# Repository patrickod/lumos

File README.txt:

A simple LED backlight for my monitor

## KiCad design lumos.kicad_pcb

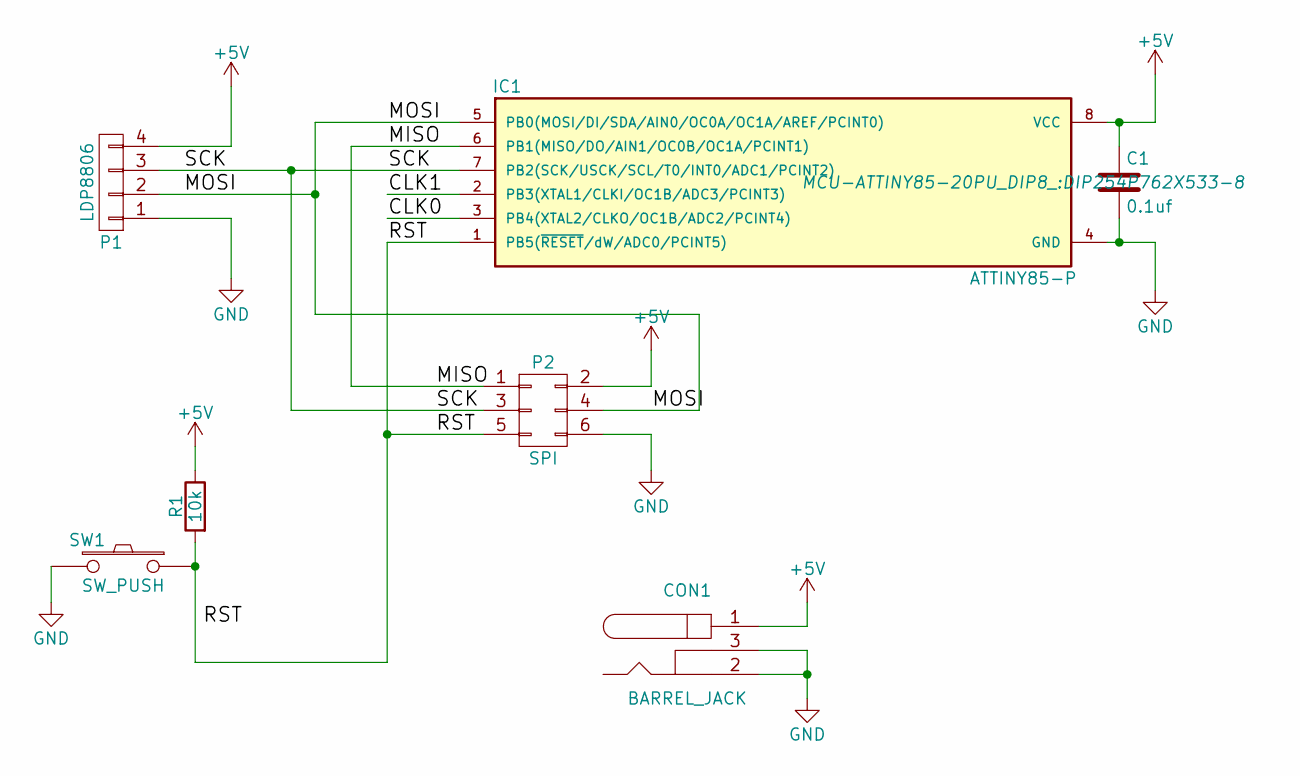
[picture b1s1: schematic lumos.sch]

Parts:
C1: 0.1uf; C_Disc_D7.5_P5
CON1: BARREL_JACK
IC1: ATTINY85-P; DIP254P762X533-8
P1: LDP8806; Pin_Header_Straight_1x04
P2: SPI; Pin_Header_Straight_2x03
R1: 10k; Resistor_Vertical_RM5mm
SW1: SW_PUSH; SW_PUSH_SMALL

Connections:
+5V: C1.1, CON1.1, IC1.8 (VCC), P1.4, P2.2, R1.1
/CLK0: IC1.3 (PB4(XTAL2/CLKO/OC1B/ADC2/PCINT4))
/CLK1: IC1.2 (PB3(XTAL1/CLKI/OC1B/ADC3/PCINT3))
/MISO: IC1.6 (PB1(MISO/DO/AIN1/OC0B/OC1A/PCINT1)), P2.1
/MOSI: IC1.5 (PB0(MOSI/DI/SDA/AIN0/OC0A/OC1A/AREF/PCI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), P1.2, P2.4
/RST: IC1.1 (PB5(~RESET~/dW/ADC0/PCINT5)), P2.5, R1.2, SW1.1
/SCK: IC1.7 (PB2(SCK/USCK/SCL/T0/INT0/ADC1/PCINT2)), P1.3, P2.3
GND: C1.2, CON1.2, CON1.3, IC1.4 (GND), P1.1, P2.6, SW1.2

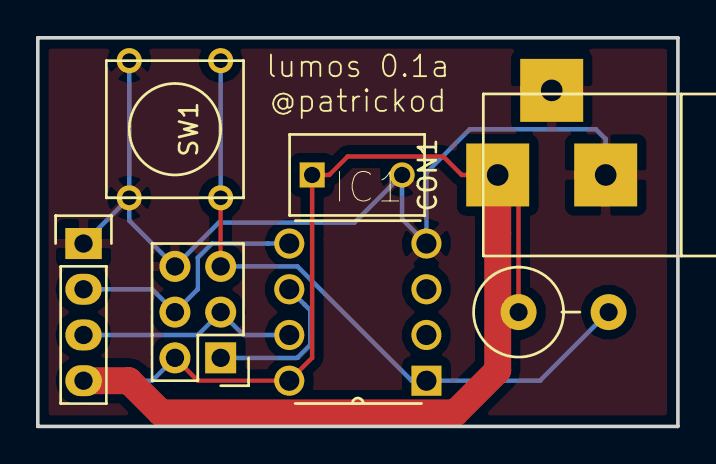
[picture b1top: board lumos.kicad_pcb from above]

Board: 2 copper layers, 35.6 x 21.6 mm, 7 parts (0 on the bottom side), 6 nets.

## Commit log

2016-02-01 Initial commit of halfway-done attiny board
2016-02-01 I have no idea what I'm doing dot jpg
2016-02-01 LICENSE everything as GPLv3
2016-02-01 Added README
2016-02-01 Project name lumos
2016-02-01 Deleted ignored files
2016-02-05 Near final layout of the lumos 0.1a board.
2016-02-05 PCB w/ traces, silk screening, updated ground on barrel jack
2016-02-05 Updated PCB w/ OSHPark's design rules.
    Generated a bunch of gerber files for OSHPark to print
2016-02-07 Updated PCB defaults for OSHPark
2016-02-08 Finalized v0.1a with output gerber assets
    lumos-v0.1a-2016-02-04.zip contains the gerber assets sent to OSHPark
    for printing.
